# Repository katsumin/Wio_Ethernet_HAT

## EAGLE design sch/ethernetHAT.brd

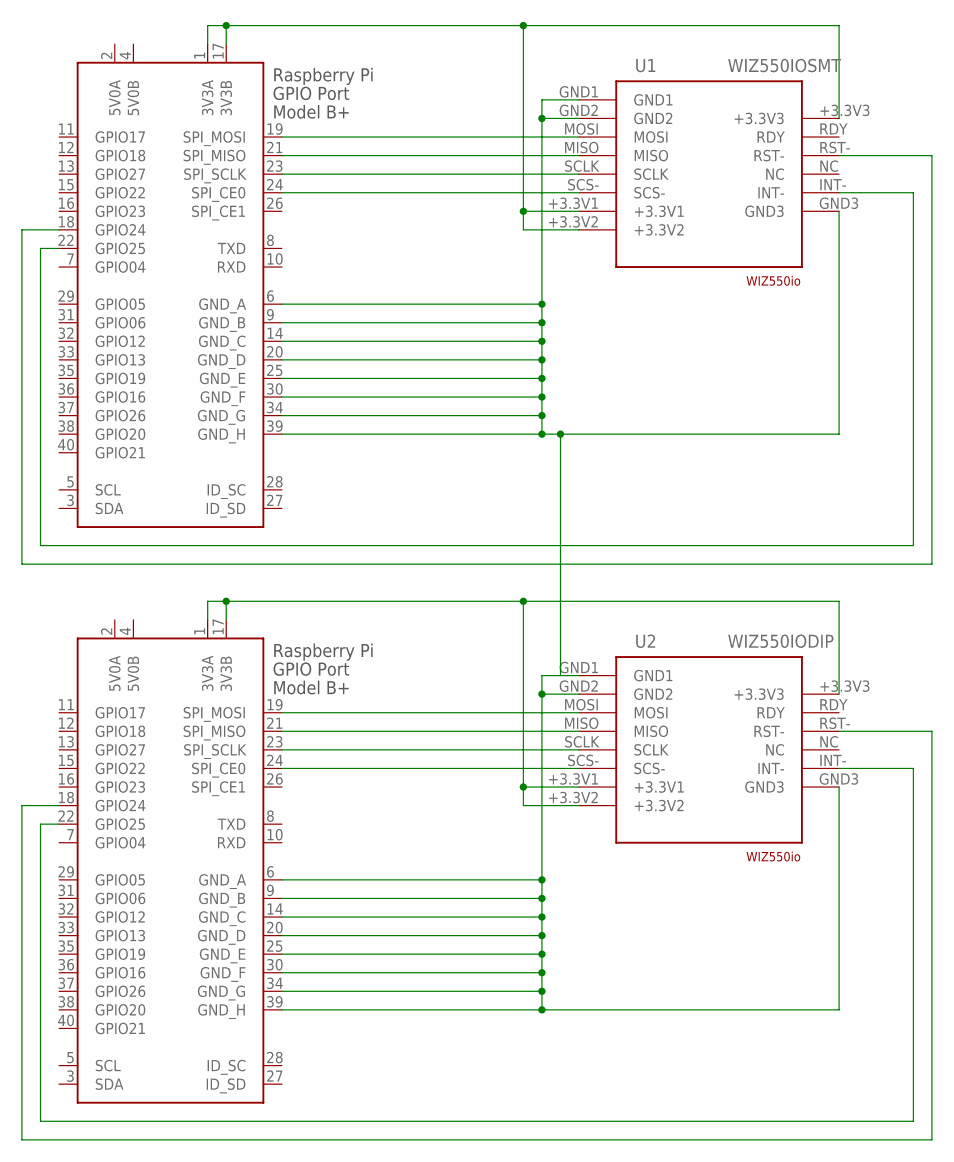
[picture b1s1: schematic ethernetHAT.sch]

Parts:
U1: WIZ550IOSMT; WIZ550IO
U2: WIZ550IODIP; WIZ550IO_A
X1, X2: RASPI_GPIO_B+#_PIN; RASPI_GPIO_B+_PIN

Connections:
3V3B: U2.+3.3V1, U2.+3.3V2, U2.+3.3V3, X2.1 (3V3A), X2.17 (3V3B)
5V0A: X1.2 (5V0A), X2.2 (5V0A)
5V0B: X1.4 (5V0B), X2.4 (5V0B)
GND: U1.GND1, U1.GND2, U1.GND3, U2.GND1, U2.GND2, U2.GND3, X1.6 (GND_A), X1.9 (GND_B), X1.14 (GND_C), X1.20 (GND_D), X1.25 (GND_E), X1.30 (GND_F), X1.34 (GND_G), X1.39 (GND_H), X2.6 (GND_A), X2.9 (GND_B), X2.14 (GND_C), X2.20 (GND_D), X2.25 (GND_E), X2.30 (GND_F), X2.34 (GND_G), X2.39 (GND_H)
INT-: U1.INT-, X1.22 (GPIO25)
MOSI: U1.MOSI, X1.19 (SPI_MOSI)
MSOI: U1.MISO, X1.21 (SPI_MISO)
unnamed: U2.MOSI, X2.19 (SPI_MOSI)
unnamed: U2.MISO, X2.21 (SPI_MISO)
unnamed: U2.SCLK, X2.23 (SPI_SCLK)
unnamed: U2.SCS-, X2.24 (SPI_CE0)
unnamed: U2.RST-, X2.18 (GPIO24)
unnamed: U2.INT-, X2.22 (GPIO25)
RST-: U1.RST-, X1.18 (GPIO24)
SCLK: U1.SCLK, X1.23 (SPI_SCLK)
SCS-: U1.SCS-, X1.24 (SPI_CE0)
VCC: U1.+3.3V1, U1.+3.3V2, U1.+3.3V3, X1.1 (3V3A), X1.17 (3V3B)

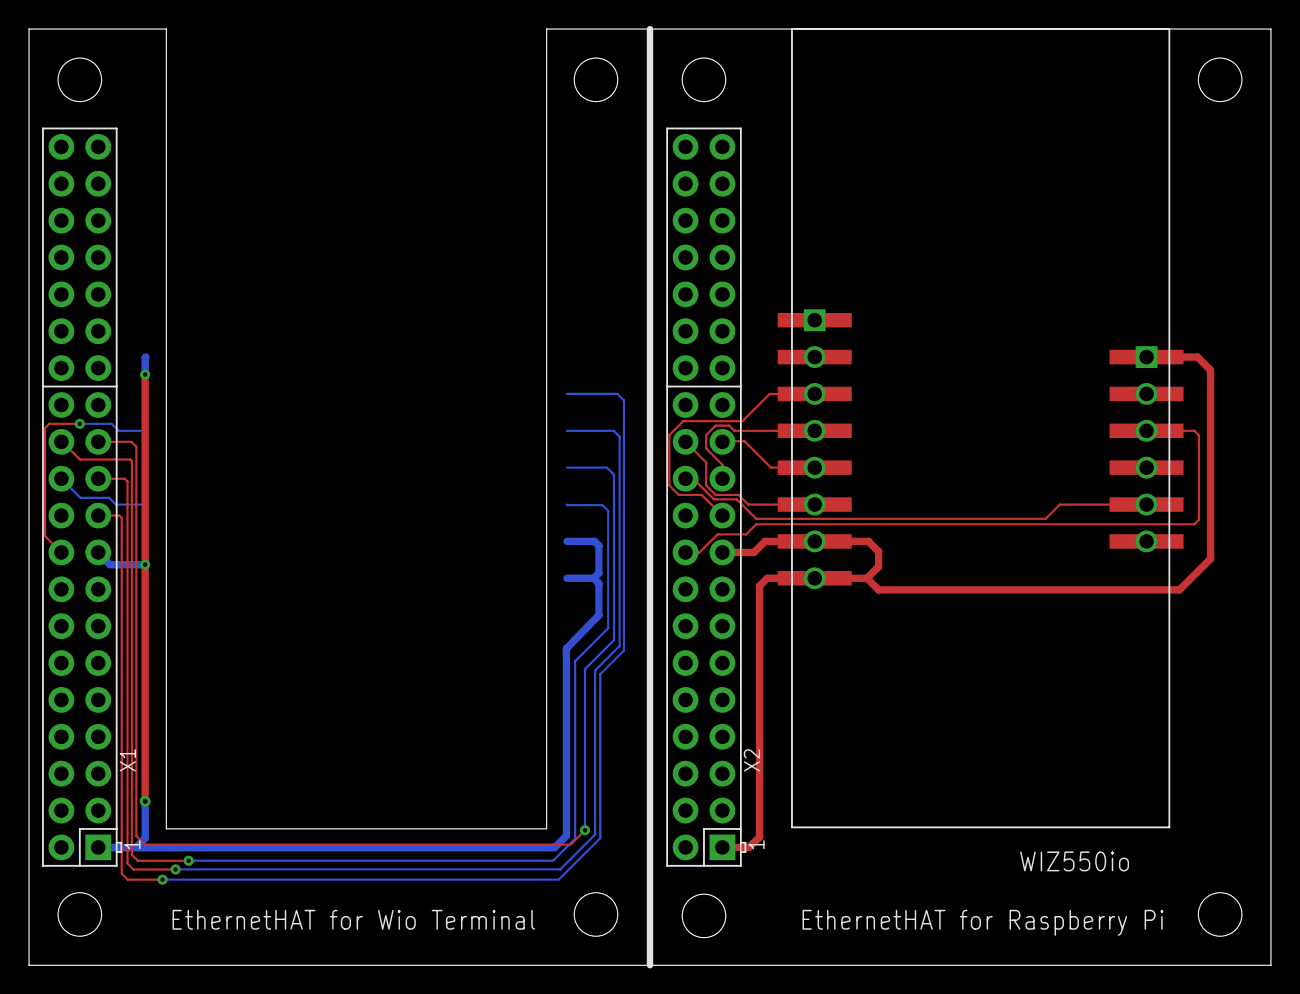
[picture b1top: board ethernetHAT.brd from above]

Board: 2 copper layers, 85.6 x 64.5 mm, 4 parts (1 on the bottom side), 17 nets.

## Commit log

2020-12-13 commit 3d models
2020-12-13 commit sch
